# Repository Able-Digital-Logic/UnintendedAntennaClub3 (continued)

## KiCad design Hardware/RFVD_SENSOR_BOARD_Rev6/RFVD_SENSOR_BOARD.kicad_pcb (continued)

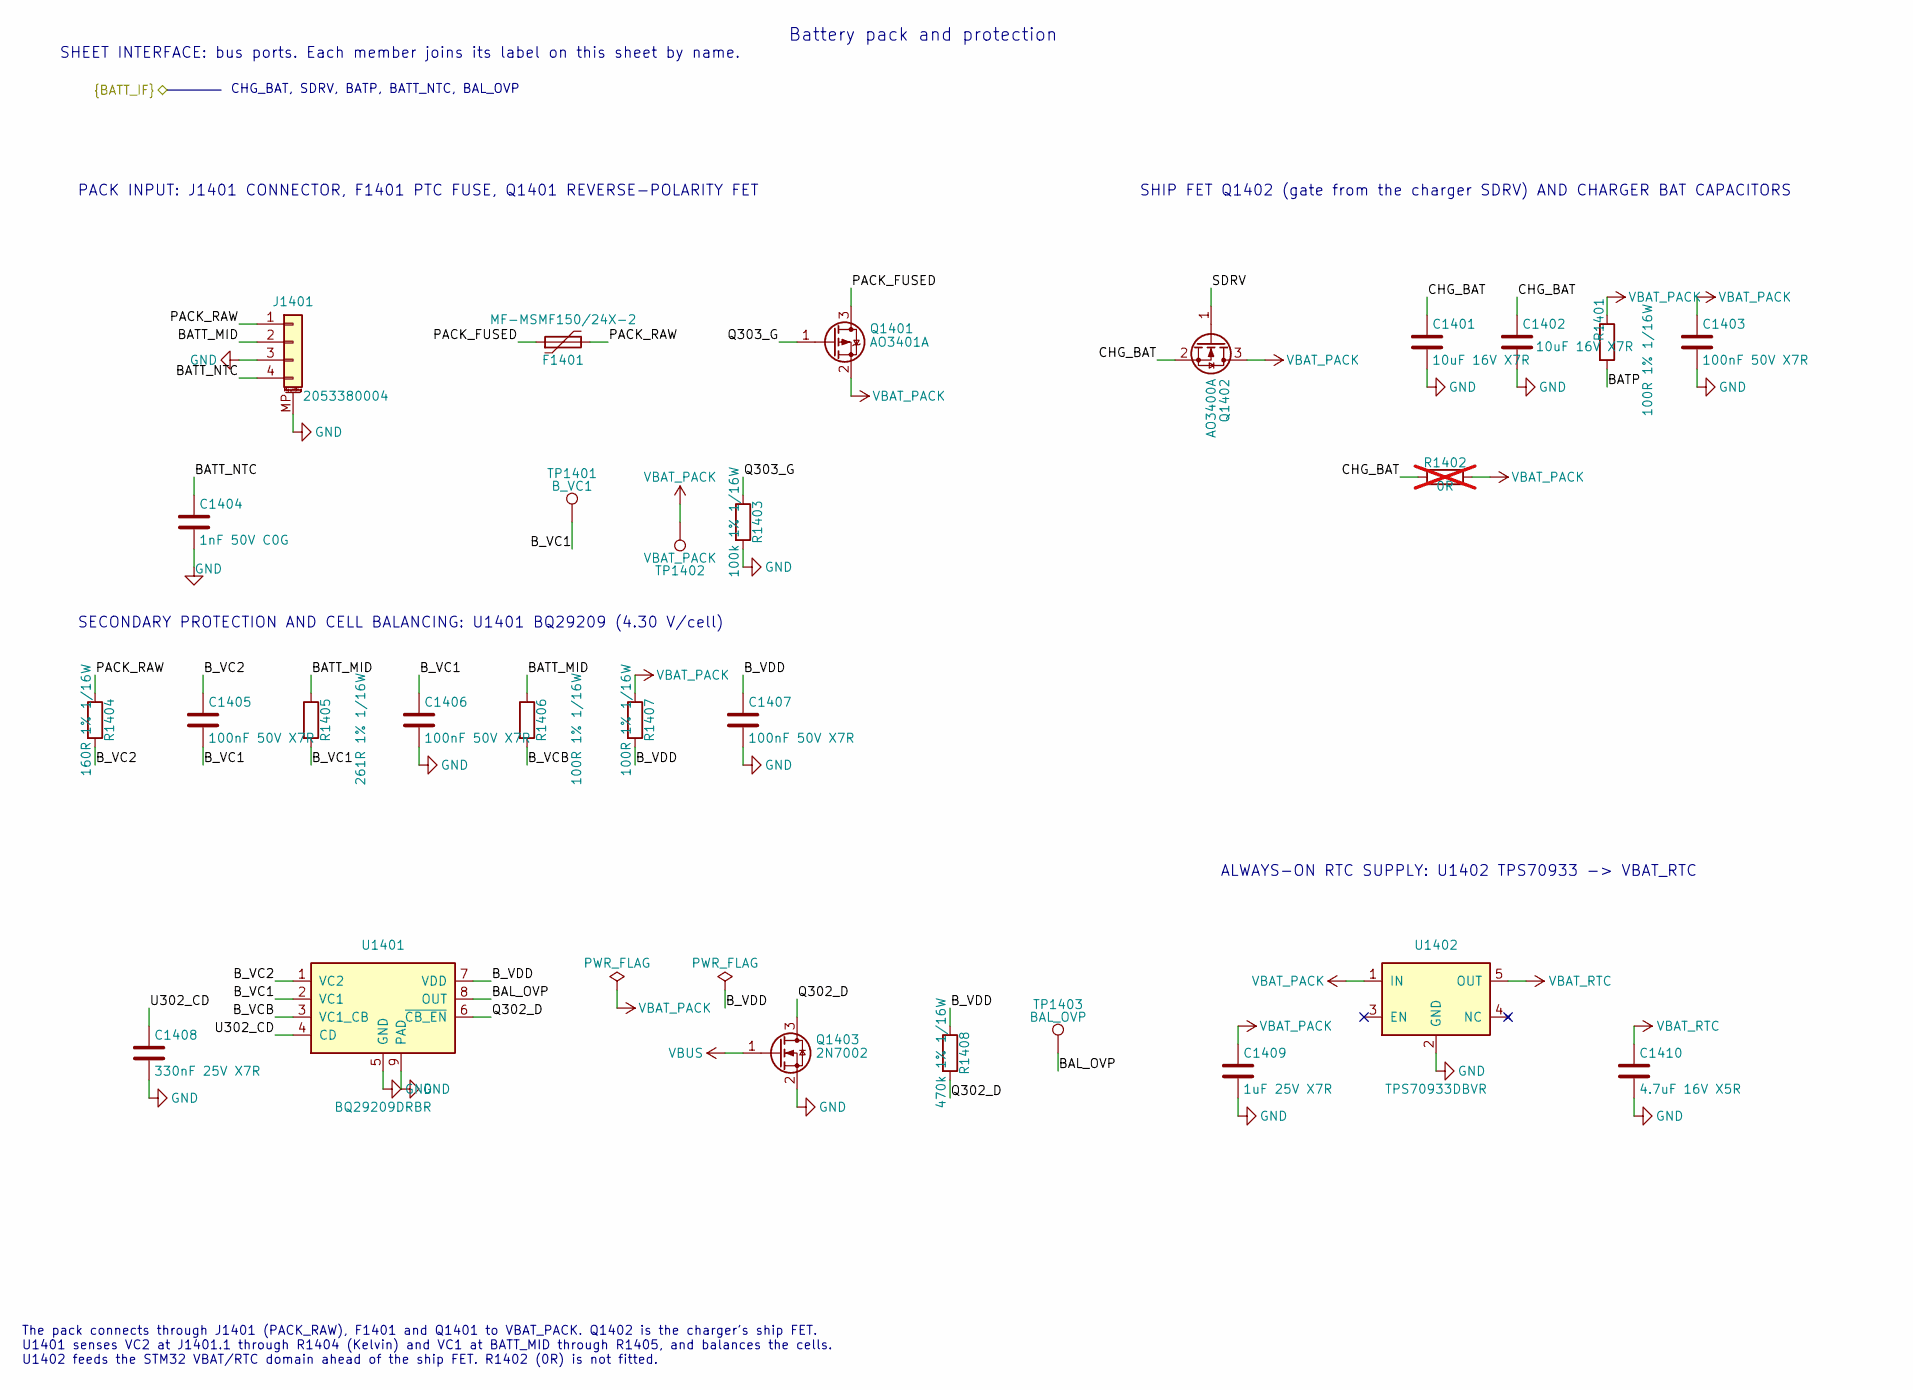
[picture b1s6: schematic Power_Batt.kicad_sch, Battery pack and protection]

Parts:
C1401, C1402: 10uF 16V X7R; C_0805_2012Metric; MPN CL21B106KOQNNNE; JLCPCB_PN C95841
C1403, C1405, C1406, C1407: 100nF 50V X7R; C_0402_1005Metric; MPN CL05B104KB54PNC; JLCPCB_PN C307331
C1404: 1nF 50V C0G; C_0402_1005Metric; MPN GRM1555C1H102JA01D; JLCPCB_PN C76947
C1408: 330nF 25V X7R; C_0603_1608Metric; MPN CC0603KRX7R8BB334; JLCPCB_PN C107070
C1409: 1uF 25V X7R; C_0603_1608Metric; MPN CL10B105KA8NNNC; JLCPCB_PN C29936
C1410: 4.7uF 16V X5R; C_0603_1608Metric; MPN CL10A475KO8NNNC; JLCPCB_PN C19666
F1401: MF-MSMF150/24X-2; Fuse_Bourns_MF-MSMF_Style2_4532Metric; MPN MF-MSMF150/24X-2; JLCPCB_PN C78695
J1401: 2053380004; Molex_Pico-Lock_205338-0004_1x04-1MP_P2.00mm_Horizontal; MPN 2053380004; JLCPCB_PN C916325
Q1401: AO3401A; SOT-23; MPN AO3401A; JLCPCB_PN C15127
Q1402: AO3400A; SOT-23; MPN AO3400A; JLCPCB_PN C20917
Q1403: 2N7002; SOT-23; MPN 2N7002; JLCPCB_PN C8545
R1401, R1406, R1407: 100R 1% 1/16W; R_0402_1005Metric; MPN 0402WGF1000TCE; JLCPCB_PN C25076
R1402: 0R; R_0805_2012Metric; not fitted
R1403: 100k 1% 1/16W; R_0402_1005Metric; MPN 0402WGF1003TCE; JLCPCB_PN C25741
R1404: 160R 1% 1/16W; R_0402_1005Metric; MPN RC0402FR-07160RL; JLCPCB_PN C327369
R1405: 261R 1% 1/16W; R_0402_1005Metric; MPN RC0402FR-07261RL; JLCPCB_PN C273335
R1408: 470k 1% 1/16W; R_0402_1005Metric; MPN RC0402FR-07470KL; JLCPCB_PN C137976
TP1401: B_VC1; TestPoint_Pad_D1.0mm; MPN PCB pad (no part)
TP1402: VBAT_PACK; TestPoint_Pad_D1.0mm; MPN PCB pad (no part)
TP1403: BAL_OVP; TestPoint_Pad_D1.0mm; MPN PCB pad (no part)
U1401: BQ29209DRBR; VSON-8-1EP_3x3mm_P0.65mm_EP1.65x2.4mm; MPN BQ29209DRBR; JLCPCB_PN C139352
U1402: TPS70933DBVR; SOT-23-5; MPN TPS70933DBVR; JLCPCB_PN C89347

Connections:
/Battery pack and protection/BAL_OVP: TP1403.1 (1_1), U1401.8 (OUT); also elsewhere on the board
/Battery pack and protection/BATP: R1401.2; also elsewhere on the board
/Battery pack and protection/BATT_MID: J1401.2, R1405.1, R1406.1
/Battery pack and protection/BATT_NTC: C1404.1, J1401.4; also elsewhere on the board
/Battery pack and protection/B_VC1: C1405.2, C1406.1, R1405.2, TP1401.1 (1_1), U1401.2 (VC1)
/Battery pack and protection/B_VC2: C1405.1, R1404.2, U1401.1 (VC2)
/Battery pack and protection/B_VCB: R1406.2, U1401.3 (VC1_CB)
/Battery pack and protection/B_VDD: C1407.1, R1407.2, R1408.1, U1401.7 (VDD)
/Battery pack and protection/CHG_BAT: C1401.1, C1402.1, Q1402.2 (S), R1402.1; also elsewhere on the board
/Battery pack and protection/PACK_FUSED: F1401.1, Q1401.3 (D)
/Battery pack and protection/PACK_RAW: F1401.2, J1401.1, R1404.1
/Battery pack and protection/Q302_D: Q1403.3 (D), R1408.2, U1401.6 (~CB_EN)
/Battery pack and protection/Q303_G: Q1401.1 (G), R1403.1
/Battery pack and protection/SDRV: Q1402.1 (G); also elsewhere on the board
/Battery pack and protection/U302_CD: C1408.1, U1401.4 (CD)
GND: C1401.2, C1402.2, C1403.2, C1404.2, C1406.2, C1407.2, C1408.2, C1409.2, C1410.2, J1401.3, J1401.MP (MountPin), Q1403.2 (S), R1403.2, U1401.5 (GND), U1401.9 (PAD), U1402.2 (GND); also elsewhere on the board
VBAT_PACK: C1403.1, C1409.1, Q1401.2 (S), Q1402.3 (D), R1401.1, R1402.2, R1407.1, TP1402.1 (1_1), U1402.1 (IN)
VBAT_RTC: C1410.1, U1402.5 (OUT); also elsewhere on the board
VBUS: Q1403.1 (G); also elsewhere on the board

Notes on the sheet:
CHG_BAT, SDRV, BATP, BATT_NTC, BAL_OVP
SHEET INTERFACE: bus ports. Each member joins its label on this sheet by name.
The pack connects through J1401 (PACK_RAW), F1401 and Q1401 to VBAT_PACK. Q1402 is the charger's ship FET. U1401 senses VC2 at J1401.1 through R1404 (Kelvin) and VC1 at BATT_MID through R1405, and balances the cells. U1402 feeds the STM32 VBAT/RTC domain ahead of the ship FET. R1402 (0R) is not fit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
ALWAYS-ON RTC SUPPLY: U1402 TPS70933 -> VBAT_RTC
SECONDARY PROTECTION AND CELL BALANCING: U1401 BQ29209 (4.30 V/cell)
SHIP FET Q1402 (gate from the charger SDRV) AND CHARGER BAT CAPACITORS
PACK INPUT: J1401 CONNECTOR, F1401 PTC FUSE, Q1401 REVERSE-POLARITY FET
Battery pack and protection

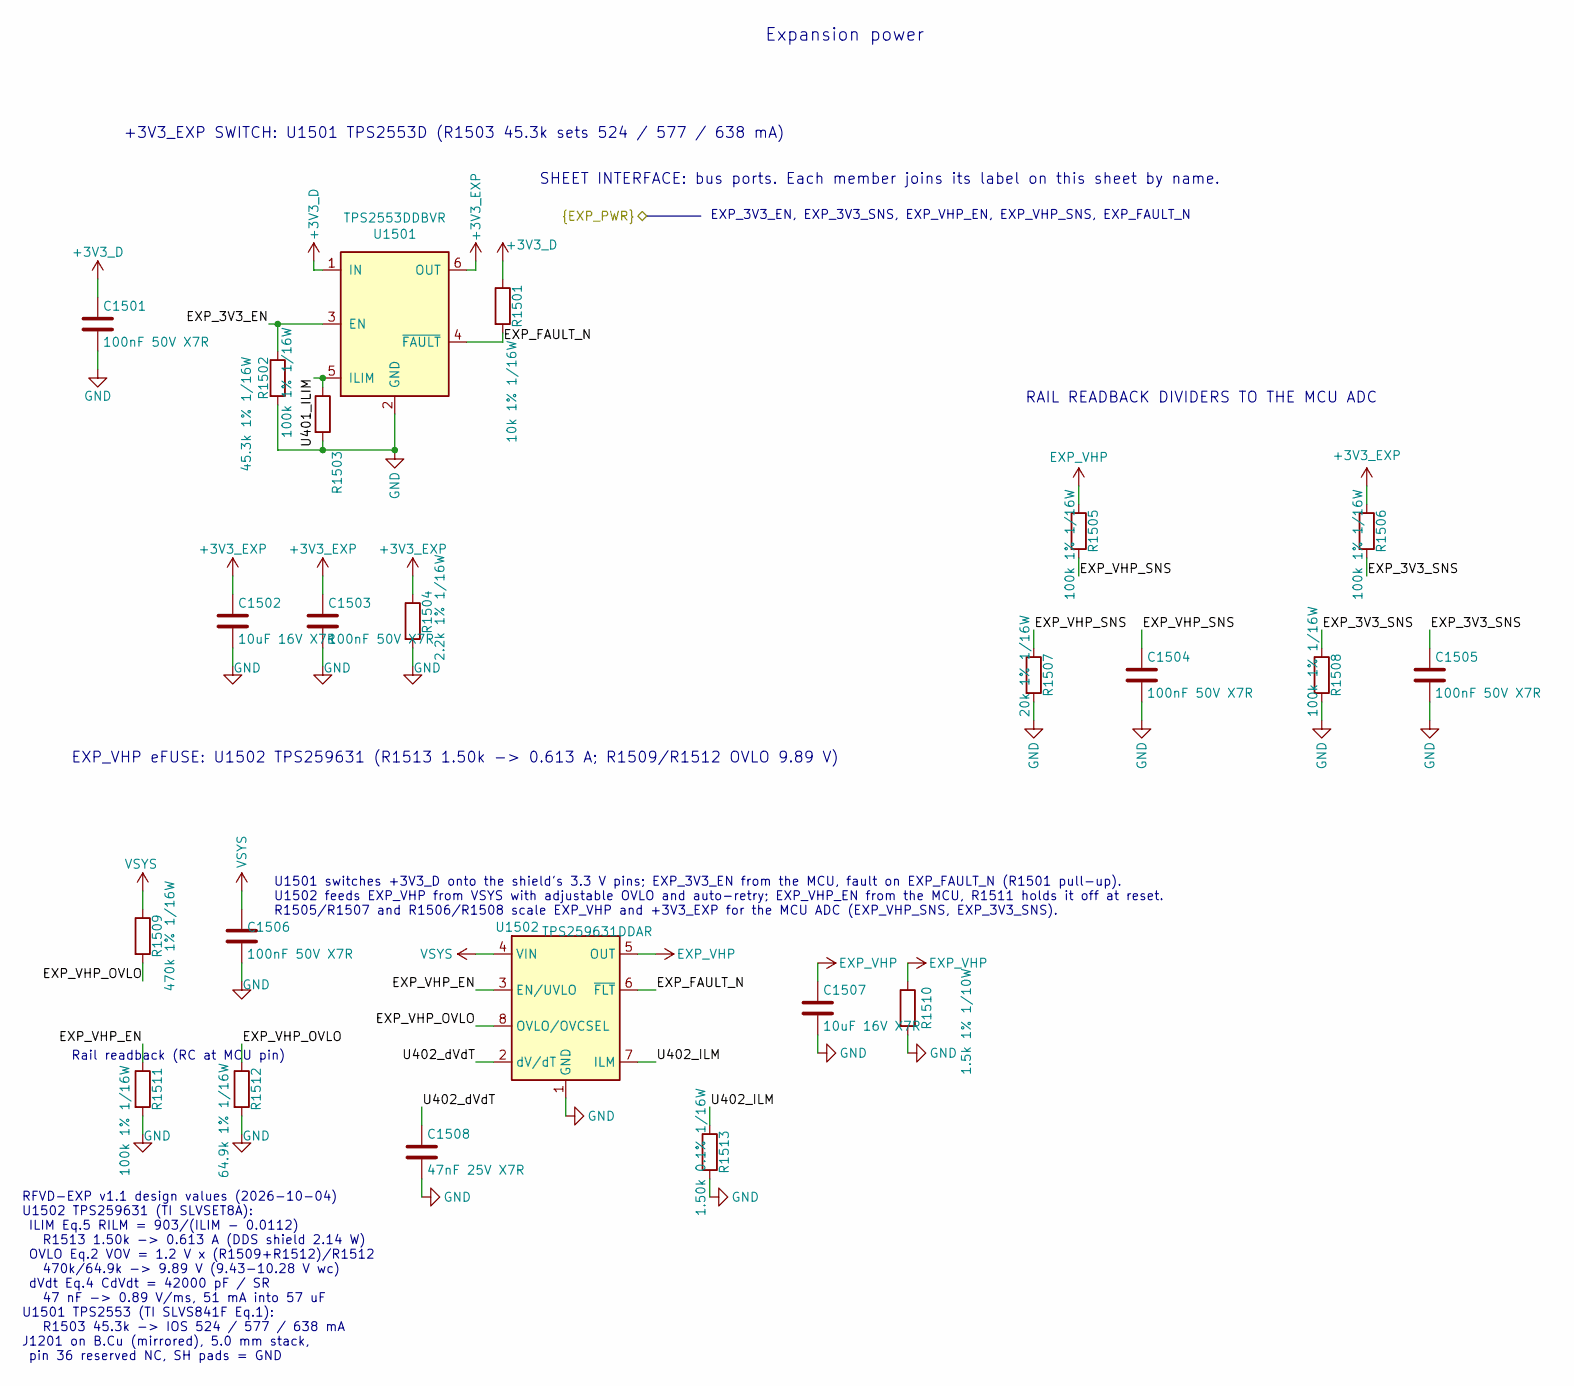
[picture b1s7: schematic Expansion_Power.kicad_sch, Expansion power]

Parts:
C1501, C1503, C1504, C1505, C1506: 100nF 50V X7R; C_0402_1005Metric; MPN CL05B104KB54PNC; JLCPCB_PN C307331
C1502, C1507: 10uF 16V X7R; C_0805_2012Metric; MPN CL21B106KOQNNNE; JLCPCB_PN C95841
C1508: 47nF 25V X7R; C_0402_1005Metric; MPN GRM155R71E473KA88D; JLCPCB_PN C77017
R1501: 10k 1% 1/16W; R_0402_1005Metric; MPN 0402WGF1002TCE; JLCPCB_PN C25744
R1502, R1505, R1506, R1508, R1511: 100k 1% 1/16W; R_0402_1005Metric; MPN 0402WGF1003TCE; JLCPCB_PN C25741
R1503: 45.3k 1% 1/16W; R_0402_1005Metric; MPN FRC0402F4532TS; JLCPCB_PN C2933099
R1504: 2.2k 1% 1/16W; R_0402_1005Metric; MPN 0402WGF2201TCE; JLCPCB_PN C25879
R1507: 20k 1% 1/16W; R_0402_1005Metric; MPN 0402WGF2002TCE; JLCPCB_PN C25765
R1509: 470k 1% 1/16W; R_0402_1005Metric; MPN RC0402FR-07470KL; JLCPCB_PN C137976
R1510: 1.5k 1% 1/10W; R_0603_1608Metric; MPN 0603WAF1501T5E; JLCPCB_PN C22843
R1512: 64.9k 1% 1/16W; R_0402_1005Metric; MPN FRC0402F6492TS; JLCPCB_PN C5713275
R1513: 1.50k 0.1% 1/16W; R_0402_1005Metric; MPN RT0402BRD071K5L; JLCPCB_PN C281775
U1501: TPS2553DDBVR; SOT-23-6; MPN TPS2553DDBVR; JLCPCB_PN C521201
U1502: TPS259631DDAR; TI_SO-PowerPAD-8_ThermalVias; MPN TPS259631DDAR; JLCPCB_PN C2155778

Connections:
+3V3_D: C1501.1, R1501.1, U1501.1 (IN); also elsewhere on the board
+3V3_EXP: C1502.1, C1503.1, R1504.1, R1506.1, U1501.6 (OUT); also elsewhere on the board
/Expansion power/EXP_3V3_EN: R1502.1, U1501.3 (EN); also elsewhere on the board
/Expansion power/EXP_3V3_SNS: C1505.1, R1506.2, R1508.1; also elsewhere on the board
/Expansion power/EXP_FAULT_N: R1501.2, U1501.4 (~FAULT), U1502.6 (~FLT); also elsewhere on the board
/Expansion power/EXP_VHP_EN: R1511.1, U1502.3 (EN/UVLO); also elsewhere on the board
/Expansion power/EXP_VHP_OVLO: R1509.2, R1512.1, U1502.8 (OVLO/OVCSEL)
/Expansion power/EXP_VHP_SNS: C1504.1, R1505.2, R1507.1; also elsewhere on the board
/Expansion power/U401_ILIM: R1503.1, U1501.5 (ILIM)
/Expansion power/U402_ILM: R1513.1, U1502.7 (ILM)
/Expansion power/U402_dVdT: C1508.1, U1502.2 (dV/dT)
EXP_VHP: C1507.1, R1505.1, R1510.1, U1502.5 (OUT); also elsewhere on the board
GND: C1501.2, C1502.2, C1503.2, C1504.2, C1505.2, C1506.2, C1507.2, C1508.2, R1502.2, R1503.2, R1504.2, R1507.2, R1508.2, R1510.2, R1511.2, R1512.2, R1513.2, U1501.2 (GND), U1502.1 (GND), U1502.9 (GND); also elsewhere on the board
VSYS: C1506.1, R1509.1, U1502.4 (VIN); also elsewhere on the board

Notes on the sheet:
RFVD-EXP v1.1 design values (2026-10-04) U1502 TPS259631 (TI SLVSET8A): ILIM Eq.5 RILM = 903/(ILIM - 0.0112) R1513 1.50k -> 0.613 A (DDS shield 2.14 W) OVLO Eq.2 VOV = 1.2 V x (R1509+R1512)/R1512 470k/64.9k -> 9.89 V (9.43-10.28 V wc) dVdt Eq.4 CdVdt = 42000 pF / SR 47 nF -> 0.89 V/ms, 51 mA into 5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
U1501 switches +3V3_D onto the shield's 3.3 V pins; EXP_3V3_EN from the MCU, fault on EXP_FAULT_N (R1501 pull-up). U1502 feeds EXP_VHP from VSYS with adjustable OVLO and auto-retry; EXP_VHP_EN from the MCU, R1511 holds it off at reset. R1505/R1507 and R1506/R1508 scale EXP_VHP and +3V3_EXP for the 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
+3V3_EXP SWITCH: U1501 TPS2553D (R1503 45.3k sets 524 / 577 / 638 mA)
RAIL READBACK DIVIDERS TO THE MCU ADC
Rail readback (RC at MCU pin)
Expansion power
EXP_3V3_EN, EXP_3V3_SNS, EXP_VHP_EN, EXP_VHP_SNS, EXP_FAULT_N
SHEET INTERFACE: bus ports. Each member joins its label on this sheet by name.
EXP_VHP eFUSE: U1502 TPS259631 (R1513 1.50k -> 0.613 A; R1509/R1512 OVLO 9.89 V)

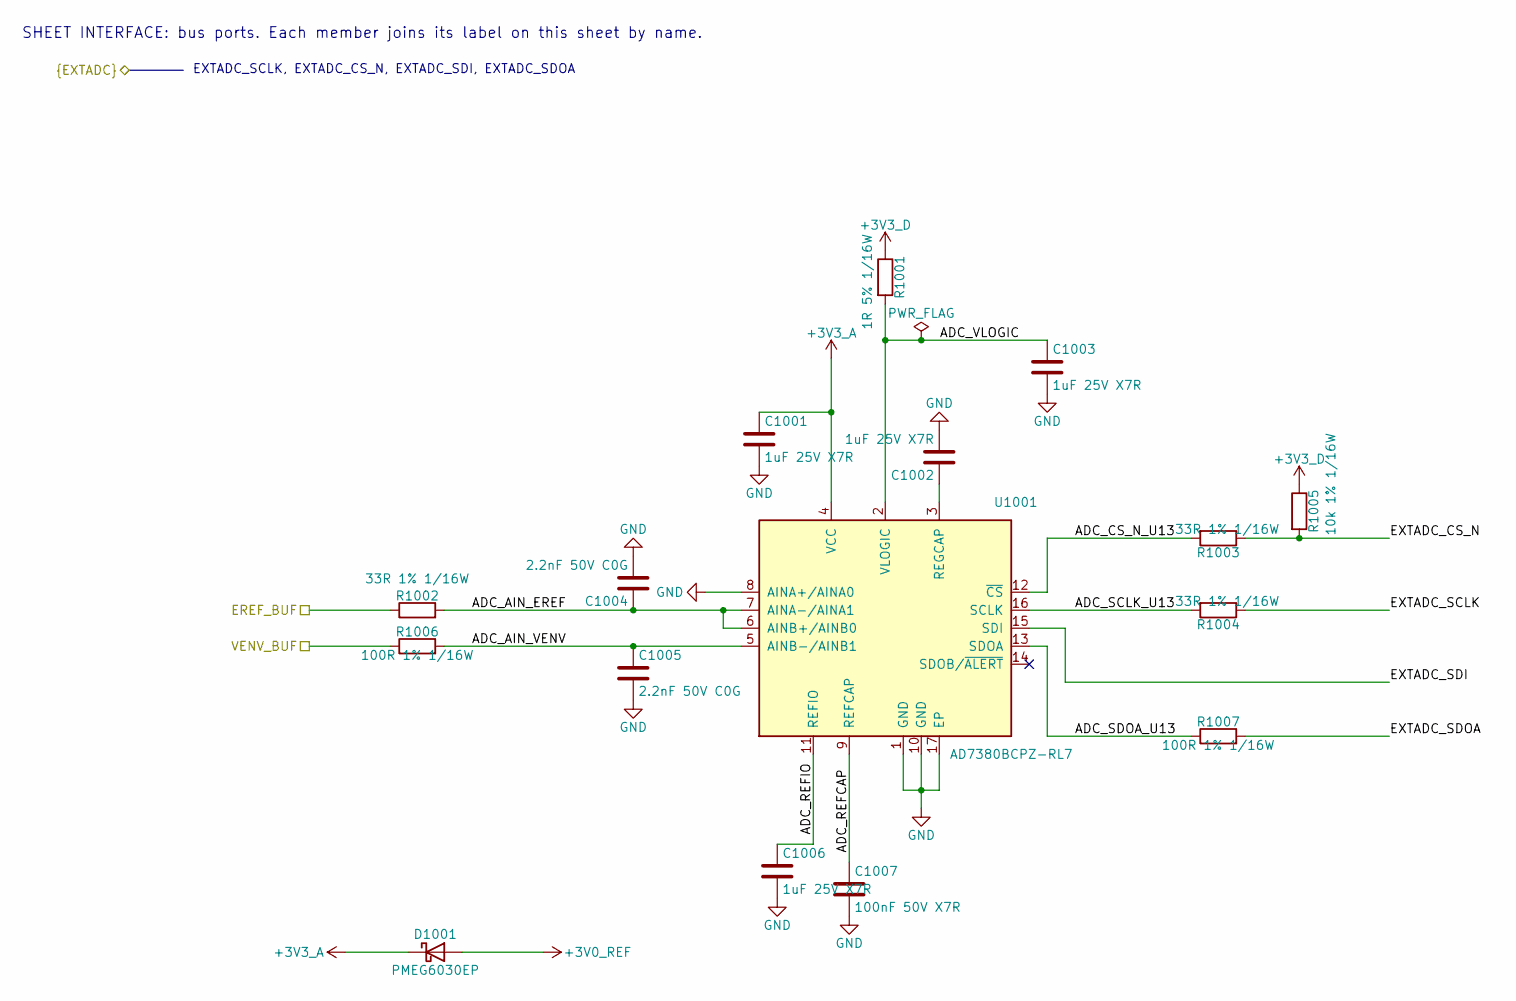
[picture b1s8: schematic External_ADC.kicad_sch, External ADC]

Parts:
C1001, C1002, C1003, C1006: 1uF 25V X7R; C_0603_1608Metric; MPN CL10B105KA8NNNC; JLCPCB_PN C29936
C1004, C1005: 2.2nF 50V C0G; C_0402_1005Metric; MPN GRM1555C1H222JA01D; JLCPCB_PN C385029
C1007: 100nF 50V X7R; C_0402_1005Metric; MPN CL05B104KB54PNC; JLCPCB_PN C307331
D1001: PMEG6030EP; D_SOD-128; MPN PMEG6030EP,115; JLCPCB_PN C456127
R1001: 1R 5% 1/16W; R_0402_1005Metric; MPN FRC0402J1R0 TS; JLCPCB_PN C2906901
R1002, R1003, R1004: 33R 1% 1/16W; R_0402_1005Metric; MPN 0402WGF330JTCE; JLCPCB_PN C25105
R1005: 10k 1% 1/16W; R_0402_1005Metric; MPN 0402WGF1002TCE; JLCPCB_PN C25744
R1006, R1007: 100R 1% 1/16W; R_0402_1005Metric; MPN 0402WGF1000TCE; JLCPCB_PN C25076
U1001: AD7380BCPZ-RL7; TQFN-16-1EP_3x3mm_P0.5mm_EP1.23x1.23mm; MPN AD7380BCPZ-RL7; JLCPCB_PN C578426

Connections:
+3V0_REF: D1001.2 (A); also elsewhere on the board
+3V3_A: C1001.1, D1001.1 (K), U1001.4 (VCC); also elsewhere on the board
+3V3_D: R1001.1, R1005.1; also elsewhere on the board
/Analog acquisition/EREF_BUF: R1002.1; also elsewhere on the board
/Analog acquisition/VENV_BUF: R1006.1; also elsewhere on the board
/External ADC/ADC_AIN_EREF: C1004.1, R1002.2, U1001.6 (AINB+/AINB0), U1001.7 (AINA-/AINA1)
/External ADC/ADC_AIN_VENV: C1005.1, R1006.2, U1001.5 (AINB-/AINB1)
/External ADC/ADC_CS_N_U13: R1003.2, U1001.12 (~CS)
/External ADC/ADC_REFCAP: C1007.1, U1001.9 (REFCAP)
/External ADC/ADC_REFIO: C1006.1, U1001.11 (REFIO)
/External ADC/ADC_SCLK_U13: R1004.2, U1001.16 (SCLK)
/External ADC/ADC_SDOA_U13: R1007.1, U1001.13 (SDOA)
/External ADC/ADC_VLOGIC: C1003.1, R1001.2, U1001.2 (VLOGIC)
/External ADC/EXTADC_CS_N: R1003.1, R1005.2; also elsewhere on the board
/External ADC/EXTADC_SCLK: R1004.1; also elsewhere on the board
/External ADC/EXTADC_SDI: U1001.15 (SDI); also elsewhere on the board
/External ADC/EXTADC_SDOA: R1007.2; also elsewhere on the board
GND: C1001.2, C1002.2, C1003.2, C1004.2, C1005.2, C1006.2, C1007.2, U1001.1 (GND), U1001.8 (AINA+/AINA0), U1001.10 (GND), U1001.17 (EP); also elsewhere on the board
unnamed: C1002.1, U1001.3 (REGCAP)

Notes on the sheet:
SHEET INTERFACE: bus ports. Each member joins its label on this sheet by name.
EXTADC_SCLK, EXTADC_CS_N, EXTADC_SDI, EXTADC_SDOA

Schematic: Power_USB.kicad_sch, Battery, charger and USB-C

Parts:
C1101: 1nF; C_0402_1005Metric; not fitted
C1102: 4.7uF 16V X5R; C_0603_1608Metric; MPN CL10A475KO8NNNC; JLCPCB_PN C19666
C1103: 1uF 25V X7R; C_0603_1608Metric; MPN CL10B105KA8NNNC; JLCPCB_PN C29936
C1104, C1105, C1109, C1110, C1111, C1114, C1115, C1116, C1117, C1118: 10uF 16V X7R; C_0805_2012Metric; MPN CL21B106KOQNNNE; JLCPCB_PN C95841
C1106, C1108, C1113: 100nF 50V X7R; C_0402_1005Metric; MPN CL05B104KB54PNC; JLCPCB_PN C307331
C1107, C1112: 47nF 25V X7R; C_0402_1005Metric; MPN GRM155R71E473KA88D; JLCPCB_PN C77017
D1101: TPD1E10B06DYAR; D_SOD-523; MPN TPD1E10B06DYAR; JLCPCB_PN C3712135
J1101: TYPE-C-31-M-12; USB_C_Receptacle_HRO_TYPE-C-31-M-12; MPN TYPE-C-31-M-12; JLCPCB_PN C165948
L1101: 1uH; L_Coilcraft_XAL4020-XXX; MPN XAL4020-102MEC; JLCPCB_PN C4555951
R1101: 51k 1% 1/16W; R_0402_1005Metric; MPN 0402WGF5102TCE; JLCPCB_PN C25794
R1102: 20k 1% 1/16W; R_0402_1005Metric; MPN 0402WGF2002TCE; JLCPCB_PN C25765
R1103: 6.04k 1% 1/16W; R_0402_1005Metric; MPN RC0402FR-076K04L; JLCPCB_PN C97819
R1104, R1112, R1113: 5.23k 1% 1/16W; R_0402_1005Metric; MPN 0402WGF5231TCE; JLCPCB_PN C25907
R1105: 30.1k 1% 1/16W; R_0402_1005Metric; MPN RC0402FR-0730K1L; JLCPCB_PN C138009
R1106: 10k; R_0402_1005Metric; not fitted
R1107, R1108: 10k 1% 1/16W; R_0402_1005Metric; MPN 0402WGF1002TCE; JLCPCB_PN C25744
R1109, R1110, R1111: 100k 1% 1/16W; R_0402_1005Metric; MPN 0402WGF1003TCE; JLCPCB_PN C25741
SW1101: B3U-1000P; SW_SPST_B3U-1000P; MPN B3U-1000P; JLCPCB_PN C231329
TP1101: POGO_D+; TestPoint_Pad_D2.0mm; MPN PCB pad (no part)
TP1102: POGO_D-; TestPoint_Pad_D2.0mm; MPN PCB pad (no part)
TP1103: POGO_GND; TestPoint_Pad_D2.0mm; MPN PCB pad (no part)
TP1104: CHG_STAT; TestPoint_Pad_D1.0mm; MPN PCB pad (no part)
TP1105: POGO_VBUS; TestPoint_Pad_D2.0mm; MPN PCB pad (no part)
U1101: BQ25798RQMR; Texas_RQM0029A_VQFN-29_4x4mm_P0.4mm; MPN BQ25798RQMR; JLCPCB_PN C2876593
U1102: TPD4E05U06DQAR; USON-10_2.5x1.0mm_P0.5mm; MPN TPD4E05U06DQAR; JLCPCB_PN C138714

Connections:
+3V3_D: R1107.1; also elsewhere on the board
/Battery pack and protection/BAL_OVP: R1110.1; also elsewhere on the board
/Battery pack and protection/BATP: U1101.18 (BATP); also elsewhere on the board
/Battery pack and protection/BATT_NTC: R1104.2, R1105.1, R1106.1, U1101.16 (TS); also elsewhere on the board
/Battery pack and protection/CHG_BAT: U1101.22 (BAT), U1101.23 (BAT); also elsewhere on the board
/Battery pack and protection/SDRV: C1101.1, U1101.24 (SDRV); also elsewhere on the board
/Battery, charger and USB-C/CC1: J1101.A5 (CC1), R1112.1, U1102.4 (D2+)
/Battery, charger and USB-C/CC2: J1101.B5 (CC2), R1113.1, U1102.5 (D2-)
/Battery, charger and USB-C/CHG_CE: R1110.2, R1111.1, U1101.13 (~CE)
/Battery, charger and USB-C/CHG_INT_N: R1107.2, U1101.21 (~INT); also elsewhere on the board
/Battery, charger and USB-C/CHG_STAT: R1108.2, TP1104.1 (1_1), U1101.1 (STAT)
/Battery, charger and USB-C/ILIM_HIZ: R1101.2, R1102.1, U1101.17 (ILIM_HIZ)
/Battery, charger and USB-C/PROG: R1103.1, U1101.20 (PROG)
/Battery, charger and USB-C/QON_N: SW1101.2, U1101.12 (~QON)
/Battery, charger and USB-C/REGN: C1102.1, R1101.1, R1104.1, R1108.1, U1101.5 (REGN)
/Battery, charger and USB-C/USB_DM: J1101.A7 (D-), J1101.B7 (D-), TP1102.1 (1_1), U1101.7 (D-), U1102.2 (D1-); also elsewhere on the board
/Battery, charger and USB-C/USB_DP: J1101.A6 (D+), J1101.B6 (D+), TP1101.1 (1_1), U1101.6 (D+), U1102.1 (D1+); also elsewhere on the board
/I2C_SCL: U1101.14 (SCL); also elsewhere on the board
/I2C_SDA: U1101.15 (SDA); also elsewhere on the board
GND: C1101.2, C1102.2, C1103.2, C1104.2, C1105.2, C1106.2, C1108.2, C1109.2, C1110.2, C1111.2, C1113.2, C1114.2, C1115.2, C1116.2, C1117.2, C1118.2, D1101.1 (A1), J1101.A1 (GND), J1101.A12 (GND), J1101.B1 (GND), J1101.B12 (GND), J1101.SH (SHIELD), R1102.2, R1103.2, R1105.2, R1106.2, R1109.1, R1111.2, R1112.2, R1113.2, SW1101.1, TP1103.1 (1_1), U1101.10 (ACDRV2), U1101.11 (ACDRV1), U1101.27 (GND), U1102.3 (GND), U1102.8 (GND); also elsewhere on the board
unnamed: C1107.1, U1101.4 (BTST1)
unnamed: C1112.1, U1101.19 (BTST2)
unnamed: C1108.1, C1109.1, C1110.1, C1111.1, U1101.29 (PMID)
unnamed: C1107.2, L1101.1, U1101.28 (SW1)
unnamed: C1112.2, L1101.2, U1101.26 (SW2)
VBUS: C1103.1, C1104.1, C1105.1, C1106.1, D1101.2 (A2), J1101.A4 (VBUS), J1101.A9 (VBUS), J1101.B4 (VBUS), J1101.B9 (VBUS), R1109.2, TP1105.1 (1_1), U1101.2 (VBUS), U1101.3 (VBUS), U1101.8 (VAC2), U1101.9 (VAC1); also elsewhere on the board
VSYS: C1113.1, C1114.1, C1115.1, C1116.1, C1117.1, C1118.1, U1101.25 (SYS); also elsewhere on the board

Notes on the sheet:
I2C_SCL, I2C_SDA
SHEET INTERFACE: bus ports. Each member joins its label on this sheet by name.
CHG_BAT, SDRV, BATP, BATT_NTC, BAL_OVP

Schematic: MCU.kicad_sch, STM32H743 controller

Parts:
C401, C402, C403, C411, C414: 100nF 50V X7R; C_0402_1005Metric; MPN CL05B104KB54PNC; JLCPCB_PN C307331
C404, C407, C408, C409, C410, C415, C417: 100nF 50V X7R; C_0402_1005Metric; MPN CL05B104KB54PNC; LCSC C307331
C405: 1nF 50V C0G; C_0402_1005Metric; MPN GRM1555C1H102JA01D; JLCPCB_PN C76947
C406, C413: 100pF 50V C0G; C_0402_1005Metric; MPN GRM1555C1H101JA01D; JLCPCB_PN C77177
C412: 10uF 16V X7R; C_0805_2012Metric; MPN CL21B106KOQNNNE; LCSC C95841
C416, C418: 1uF 25V X7R; C_0603_1608Metric; MPN CL10B105KA8NNNC; LCSC C29936
C419, C420: 2.2uF 16V X5R; C_0603_1608Metric; MPN CL10A225KO8NNNC; JLCPCB_PN C23630
C421, C422: 10pF 50V C0G; C_0402_1005Metric; MPN CL05C100JB5NNNC; JLCPCB_PN C32949
R401: 10k 1% 1/16W; R_0402_1005Metric; MPN 0402WGF1002TCE; LCSC C25744
R402: 33R 1% 1/16W; R_0402_1005Metric; MPN 0402WGF330JTCE; JLCPCB_PN C25105
R403: 10k 1% 1/16W; R_0402_1005Metric; MPN 0402WGF1002TCE; JLCPCB_PN C25744
R404: 1k 1% 1/16W; R_0402_1005Metric; MPN 0402WGF1001TCE; JLCPCB_PN C11702
R405, R406, R408: 330R 1% 1/16W; R_0402_1005Metric; MPN 0402WGF3300TCE; JLCPCB_PN C25104
R407, R409: 100k 0.1% 1/10W; R_0603_1608Metric; MPN RT0603BRD07100KL; JLCPCB_PN C122538
U401: STM32H743VIT6; LQFP-100_14x14mm_P0.5mm; MPN STM32H743VIT6; JLCPCB_PN C114409
Y401: 12MHz 3.3V CMOS; Oscillator_SMD_Abracon_ASE-4Pin_3.2x2.5mm; MPN ASE-12.000MHZ-LC-T; JLCPCB_PN C596950
Y402: 32.768kHz 7pF; Crystal_SMD_Abracon_ABS05-2Pin_1.6x1.0mm; MPN Q-SC16S0322070AAAN; JLCPCB_PN C5221452

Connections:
+3V0_REF: C417.1, C418.1, U401.20 (VREF+); also elsewhere on the board
+3V3_A: C415.1, C416.1, U401.21 (VDDA); also elsewhere on the board
+3V3_D: C402.1, C403.1, C407.1, C408.1, C409.1, C410.1, C411.1, C412.1, R403.2, U401.11 (VDD), U401.27 (VDD), U401.50 (VDD), U401.75 (VDD), U401.100 (VDD), Y401.1 (EN), Y401.4 (Vdd); also elsewhere on the board
+5V_A: R409.1; also elsewhere on the board
/3.3 V supplies/BUCK_PG: U401.84 (PD3); also elsewhere on the board
/3.3 V supplies/BUCK_SYNC: R404.2; also elsewhere on the board
/3.3 V supplies/LDO_EN: U401.7 (PC13); also elsewhere on the board
/Analog acquisition/ADC_EREF: U401.32 (PC4); also elsewhere on the board
/Analog acquisition/ADC_VENV: U401.30 (PA6); also elsewhere on the board
/Battery, charger and USB-C/CHG_INT_N: C405.1, U401.22 (PA0); also elsewhere on the board
/Battery, charger and USB-C/USB_DM: U401.70 (PA11); also elsewhere on the board
/Battery, charger and USB-C/USB_DP: U401.71 (PA12); also elsewhere on the board
/Expansion mezzanine/EXP_ANA_MON_MCU: U401.15 (PC0); also elsewhere on the board
/Expansion mezzanine/EXP_CS0_N_MCU: U401.51 (PB12); also elsewhere on the board
/Expansion mezzanine/EXP_CS1_N_MCU: U401.55 (PD8); also elsewhere on the board
/Expansion mezzanine/EXP_DETECT_N_MCU: U401.90 (PB4); also elsewhere on the board
/Expansion mezzanine/EXP_GATE_MCU: U401.29 (PA5); also elsewhere on the board
/Expansion mezzanine/EXP_INT0_N_MCU: U401.56 (PD9); also elsewhere on the board
/Expansion mezzanine/EXP_INT1_N_MCU: U401.57 (PD10); also elsewhere on the board
/Expansion mezzanine/EXP_IO0_MCU: U401.98 (PE1); also elsewhere on the board
/Expansion mezzanine/EXP_IO1_MCU: U401.97 (PE0); also elsewhere on the board
/Expansion mezzanine/EXP_MISO_MCU: U401.53 (PB14); also elsewhere on the board
/Expansion mezzanine/EXP_MOSI_MCU: U401.54 (PB15); also elsewhere on the board
/Expansion mezzanine/EXP_RST_N_MCU: U401.91 (PB5); also elsewhere on the board
/Expansion mezzanine/EXP_SCK_MCU: U401.52 (PB13); also elsewhere on the board
/Expansion mezzanine/EXP_SYNC_MCU: U401.93 (PB7); also elsewhere on the board
/Expansion mezzanine/EXP_TMR0_MCU: U401.67 (PA8); also elsewhere on the board
/Expansion mezzanine/EXP_TMR1_MCU: U401.64 (PC7); also elsewhere on the board
/Expansion mezzanine/EXP_TMR_IN_MCU: U401.77 (PA15); also elsewhere on the board
/Expansion power/EXP_3V3_EN: U401.45 (PE15); also elsewhere on the board
/Expansion power/EXP_3V3_SNS: U401.18 (PC3_C); also elsewhere on the board
/Expansion power/EXP_FAULT_N: U401.87 (PD6); also elsewhere on the board
/Expansion power/EXP_VHP_EN: U401.13 (PH1); also elsewhere on the board
/Expansion power/EXP_VHP_SNS: U401.17 (PC2_C); also elsewhere on the board
/External ADC/EXTADC_CS_N: U401.41 (PE11); also elsewhere on the board
/External ADC/EXTADC_SCLK: U401.42 (PE12); also elsewhere on the board
/External ADC/EXTADC_SDI: U401.43 (PE13); also elsewhere on the board
/External ADC/EXTADC_SDOA: U401.44 (PE14); also elsewhere on the board
/I2C_SCL: U401.95 (PB8); also elsewhere on the board
/I2C_SDA: U401.96 (PB9); also elsewhere on the board
/Programming and service/NRST: C404.1, U401.14 (NRST); also elsewhere on the board
/Programming and service/SWCLK: U401.76 (PA14); also elsewhere on the board
/Programming and service/SWDIO: U401.72 (PA13); also elsewhere on the board
/SD and capture memory/PSRAM_CLK_MCU: U401.36 (PB2); also elsewhere on the board
/SD and capture memory/PSRAM_CS_N: U401.92 (PB6); also elsewhere on the board
/SD and capture memory/PSRAM_IO0_MCU: U401.58 (PD11); also elsewhere on the board
/SD and capture memory/PSRAM_IO1_MCU: U401.59 (PD12); also elsewhere on the board
/SD and capture memory/PSRAM_IO2_MCU: U401.1 (PE2); also elsewhere on the board
/SD and capture memory/PSRAM_IO3_MCU: U401.60 (PD13); also elsewhere on the board
/SD and capture memory/SD_CD_N: U401.4 (PE5); also elsewhere on the board
/SD and capture memory/SD_CLK_MCU: U401.80 (PC12); also elsewhere on the board
/SD and capture memory/SD_CMD_MCU: U401.83 (PD2); also elsewhere on the board
/SD and capture memory/SD_D0_MCU: U401.65 (PC8); also elsewhere on the board
/SD and capture memory/SD_D1_MCU: U401.66 (PC9); also elsewhere on the board
/SD and capture memory/SD_D2_MCU: U401.78 (PC10); also elsewhere on the board
/SD and capture memory/SD_D3_MCU: U401.79 (PC11); also elsewhere on the board
/STM32H743 controller/BOOT0: R401.1, U401.94 (BOOT0)
/STM32H743 controller/BUCK_SYNC_MCU: R404.1, U401.35 (PB1)
/STM32H743 controller/LCD_BL: U401.63 (PC6); also elsewhere on the board
/STM32H743 controller/LCD_CS_N_MCU: U401.88 (PD7); also elsewhere on the board
/STM32H743 controller/LCD_D0_MCU: U401.61 (PD14); also elsewhere on the board
/STM32H743 controller/LCD_D1_MCU: U401.62 (PD15); also elsewhere on the board
/STM32H743 controller/LCD_D2_MCU: U401.81 (PD0); also elsewhere on the board
/STM32H743 controller/LCD_D3_MCU: U401.82 (PD1); also elsewhere on the board
/STM32H743 controller/LCD_D4_MCU: U401.37 (PE7); also elsewhere on the board
/STM32H743 controller/LCD_D5_MCU: U401.38 (PE8); also elsewhere on the board
/STM32H743 controller/LCD_D6_MCU: U401.39 (PE9); also elsewhere on the board
/STM32H743 controller/LCD_D7_MCU: U401.40 (PE10); also elsewhere on the board
/STM32H743 controller/LCD_DC_MCU: U401.5 (PE6); also elsewhere on the board
/STM32H743 controller/LCD_RST: R405.2; also elsewhere on the board
/STM32H743 controller/LCD_RST_MCU: C406.1, R405.1, U401.24 (PA2)
/STM32H743 controller/LCD_WR_N_MCU: U401.86 (PD5); also elsewhere on the board
/STM32H743 controller/MARK_N_MCU: U401.3 (PE4); also elsewhere on the board
/STM32H743 controller/RECORD_N_MCU: U401.2 (PE3); also elsewhere on the board
/STM32H743 controller/TP_INT: R408.2; also elsewhere on the board
/STM32H743 controller/TP_INT_MCU: R408.1, U401.31 (PA7)
/STM32H743 controller/TP_RST: R406.2; also elsewhere on the board
/STM32H743 controller/TP_RST_MCU: C413.1, R406.1, U401.25 (PA3)
/STM32H743 controller/TP_SCL: U401.46 (PB10); also elsewhere on the board
/STM32H743 controller/TP_SDA: U401.47 (PB11); also elsewhere on the board
/STM32H743 controller/UI_EN: U401.33 (PC5); also elsewhere on the board
/STM32H743 controller/UI_FAULT_N: U401.34 (PB0); also elsewhere on the board
/STM32H743 controller/VCAP: C419.1, C420.1, U401.48 (VCAP), U401.73 (VCAP)
GND: C401.2, C402.2, C403.2, C404.2, C405.2, C406.2, C407.2, C408.2, C409.2, C410.2, C411.2, C412.2, C413.2, C414.2, C415.2, C416.2, C417.2, C418.2, C419.2, C420.2, C421.2, C422.2, R401.2, R407.2, U401.10 (VSS), U401.19 (VSSA), U401.26 (VSS), U401.49 (VSS), U401.74 (VSS), U401.99 (VSS), Y401.2 (GND); also elsewhere on the board
unnamed: R403.1, U401.28 (PA4)
unnamed: C414.1, R407.1, R409.2, U401.16 (PC1)
unnamed: C422.1, U401.8 (PC14), Y402.2
unnamed: C421.1, U401.9 (PC15), Y402.1
unnamed: R402.2, U401.12 (PH0)
unnamed: R402.1, Y401.3 (OUT)
VBAT_RTC: C401.1, U401.6 (VBAT); also elsewhere on the board

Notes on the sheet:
MCU <-> Service
Y401,R402,C419,C420 and rails
I/O
UI_EN, UI_FAULT_N, RECORD_N_MCU, MARK_N_MCU
Signal / bus
Memory clock and selection.
Optional edge timestamp; not ADC clock.
100 nF at each VDD pin; 10 uF bulk.
SHEET INTERFACE: bus ports. Each member joins its label on this sheet by name.
SWD / UART / boot/reset
MCU <-> Storage
Purpose
Source / destination
EXP_SCK/MOSI/MISO_MCU, EXP_CS0/CS1_N_MCU, EXP_INT0/INT1_N_MCU, EXP_IO0/IO1_MCU, EXP_TMR0/TMR1/TMR_IN_MCU, EXP_GATE/SYNC/ANA_MON/RST_N/DETECT_N_MCU
ADC_VENV / ADC_EREF
MCU -> Storage
Analog -> PA6 / PC4
OUT
C908 (DNP RC footprint on TP_INT_MCU) deleted (S-9): R408 330R stays the only TP_INT conditioning. PA7 is driven low (output) during RECORD. PD4 (pin 85) unused: display bus is write-only (S-11).
EXTADC_SCLK, EXTADC_CS_N, EXTADC_SDI, EXTADC_SDOA
Module interfaces
User actions and module status.
VDDA / VREF+ decoupling
VCAP1/2 tied (net VCAP, AN4938); 2.2 uF at each pin; no external loads.
LOCAL / PWR
PSRAM IO*_MCU / SD CMD,DAT
ADC3 monitors EXP_ANA_MON (PC0) and analog 5 V (2:1 divider, PC1). VBAT/VSYS: U1101 BQ25798 ADC over I2C1. Apply rail-validity and startup guards.
Open-drain control and sensor buses.
Programming, diagnosis and recovery.
TRIGGER_CAPTURE
Screen data, reset, backlight and power.
SD CLK / card detect
LCD_D0..D7_MCU, LCD_WR_N_MCU, LCD_DC_MCU, LCD_CS_N_MCU, LCD_RST, LCD_BL
LCD controls / UI_EN
Buffered capture and card transfers.
OUT / IN
R409/R407 -> ADC3 (+5V_A)
PSRAM_CLK_MCU, PSRAM_CS_N, PSRAM_IO0..IO3_MCU
PSRAM CLK / CE
Buttons / IRQ / UI fault

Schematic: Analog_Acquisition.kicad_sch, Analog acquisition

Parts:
C501: 510pF 50V C0G 1%; C_0603_1608Metric; Tolerance 1%; Voltage Rating 50V; MPN CC0603FRNPO9BN511; JLCPCB_PN C519572
C502: 1.2nF 50V C0G 1%; C_0603_1608Metric; Tolerance 1%; Voltage Rating 50V; MPN GCM1885C1H122FA16D; JLCPCB_PN C1517816
C503, C504: 470pF 50V C0G 1%; C_0603_1608Metric; Tolerance 1%; Voltage Rating 50V; MPN CC0603FRNPO9BN471; JLCPCB_PN C519564
C505, C507: 2.2nF 50V C0G; C_0402_1005Metric; Tolerance 5%; Voltage Rating 50V; MPN GRM1555C1H222JA01D; JLCPCB_PN C385029
C506: 10nF 50V C0G; C_0603_1608Metric; Tolerance 1%; Voltage Rating 50V; MPN GRM1885C1H103JA01D; JLCPCB_PN C85973
C508, C512, C513: 100nF 50V X7R; C_0402_1005Metric; MPN CL05B104KB54PNC; LCSC C307331
C509: 1uF 25V X7R; C_0603_1608Metric; MPN CL10B105KA8NNNC; LCSC C29936
C510: 1uF 25V film; C_1206_3216Metric; MPN 25MU105MA23216; LCSC C3776619
C511: 4.7uF 25V X7R; C_0805_2012Metric; MPN C2012X7R1E475KT000N; LCSC C76642
C514, C516: 1uF 25V X7R; C_0603_1608Metric; Tolerance 10%; Voltage Rating 25V; MPN CL10B105KA8NNNC; JLCPCB_PN C29936
C515: 100nF 50V X7R; C_0402_1005Metric; Tolerance 10%; Voltage Rating 50V; MPN CL05B104KB54PNC; JLCPCB_PN C307331
R501, R502: 2.26k 0.1% 1/10W; R_0603_1608Metric; Power Rating 0.1W at 70C; Tolerance 0.1%; MPN PTFR0603B2K26P9; JLCPCB_PN C47115856
R503, R504: 1.33k 0.1% 1/10W; R_0603_1608Metric; Power Rating 0.1W at 70C; Tolerance 0.1%; MPN RT0603BRD071K33L; JLCPCB_PN C861196
R505: 33R 1% 1/10W; R_0603_1608Metric; Power Rating 0.1W at 70C; Tolerance 1%; MPN 0603WAF330JT5E; JLCPCB_PN C23140
R506: 22.6k 0.1% 1/10W; R_0603_1608Metric; Tolerance 0.1%; Power Rating 0.1W at 70C; MPN RT0603BRD0722K6L; JLCPCB_PN C861236
R507: 33R 1% 1/10W; R_0603_1608Metric; Tolerance 1%; Power Rating 0.1W at 70C; MPN 0603WAF330JT5E; JLCPCB_PN C23140
R508: 1R 5% 1/16W; R_0402_1005Metric; MPN FRC0402J1R0 TS; LCSC C2906901
TP501: VENV_RAW; TestPoint_Pad_D1.0mm; MPN DNP-NO-COMPONENT; LCSC N/A
TP502: VENV_BUF; TestPoint_Pad_D1.0mm; MPN PCB_PAD
TP503: EREF_RAW; TestPoint_Pad_D1.0mm; MPN DNP-NO-COMPONENT; LCSC N/A
TP504: +3V0_REF; TestPoint_Pad_D1.0mm; MPN DNP-NO-COMPONENT; LCSC N/A
TP505: GND_ANALOG; TestPoint_Pad_D1.0mm; MPN PCB_PAD
U501, U502: OPA2320; VSSOP-8_3x3mm_P0.65mm; MPN OPA2320AIDGKR; LCSC C545235
U503: REF5030IDR; SOIC-8_3.9x4.9mm_P1.27mm; MPN REF5030IDR; LCSC C2878155

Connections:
+3V0_REF: C512.1, R508.1, TP504.1 (1_1), U503.6 (Vout); also elsewhere on the board
+3V3_A: C513.1, C514.1, C515.1, C516.1, U501.8 (V+), U502.8 (V+); also elsewhere on the board
+5V_A: C508.1, C509.1, U503.2 (Vin); also elsewhere on the board
/Analog acquisition/ADC_EREF: C507.1, R507.2; also elsewhere on the board
/Analog acquisition/ADC_VENV: C505.1, R505.2; also elsewhere on the board
/Analog acquisition/EREF_BUF: R507.1, U502.6 (-), U502.7 (OUT); also elsewhere on the board
/Analog acquisition/EREF_RAW: R506.1, TP503.1 (1_1); also elsewhere on the board
/Analog acquisition/VENV_BUF: C502.2, R505.1, TP502.1 (1_1), U501.6 (-), U501.7 (OUT); also elsewhere on the board
/Analog acquisition/VENV_RAW: R501.1, TP501.1 (1_1); also elsewhere on the board
GND: C503.2, C504.2, C505.2, C506.2, C507.2, C508.2, C509.2, C510.2, C511.2, C512.2, C513.2, C514.2, C515.2, C516.2, TP505.1 (1_1), U501.4 (V-), U502.4 (V-), U503.4 (GND); also elsewhere on the board
unnamed: C501.1, R501.2, R502.1
unnamed: C502.1, R503.2, R504.1
unnamed: C511.1, R508.2
unnamed: C503.1, R502.2, U501.3 (+)
unnamed: C501.2, R503.1, U501.1 (OUT), U501.2 (-)
unnamed: C504.1, R504.2, U501.5 (+)
unnamed: C506.1, R506.2, U502.3 (+), U502.5 (+)
unnamed: U502.1 (OUT), U502.2 (-)
unnamed: C510.1, U503.5 (Trim/NR)

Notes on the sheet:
TP503/TP501: raw pair. ADC pair: probe C505 / C507 pad 1 (TP7/TP6 removed). TP502: envelope buffer. Use high-impedance probes and account for their loading.
Purpose
Power -> U503 / U502,U501
LOCAL
Filtered pair; probe C505 / C507 pad 1.
Reference and amplifier supplies.
R505 / R507 -> MCU
PWR
RF input -> R501 / R506
VENV_RAW / EREF_RAW
Envelope and reference filter inputs.
+3V0_REF
Signal / bus
PWR IN
Shared conversion reference.
Common ground plane
GND
Envelope output before ADC isolation.
U503 -> MCU VREF+
I/O
Module interfaces
ADC_VENV / ADC_EREF
Filter resistors: 0.1%; filter capacitors: C0G 1% (C506 EREF pole and C507/C505 ADC reservoirs: C0G 5%). ADC range: AD7380 0 to 2.5 V (internal reference, S-26); U401 ADC 0 to +3V0_REF. Amplifier overdrive can clip the ADC; check both channels during calibration.
U501 / U502 filter loops
Envelope and reference filters
VENV_BUF / TP502
Unity-gain Sallen-Key feedback.
ADC inputs -> GND
About 95 kHz modeled envelope bandwidth. Apply digital filtering before decimation. Qualify settling, clipping and noise on the assembled board.
Each output -> its minus input
PWR OUT
U501 pin 7 -> R505
C505 / C507
Local charge reservoirs after 47R.
OUT
Keep bypass and feedback returns local.
100 nF + 1 uF at each dual amplifier supply. Both packages use +3V3_A.
Source / destination
+5V_A / +3V3_A
